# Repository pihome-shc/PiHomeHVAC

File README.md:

# MaxAir - Smart Thermostat

### Note: Now at Version 3.23

The previous version, PiHome, was centered around the creation of zones, this version is more centered around devices.

Version 1.1 introduces the 'Switch' zone category. These zones uses a binary switch sensor to control a zone relay and can be used to perform Home Automation tasks.

Version 1.2 Introduces the ability the control schedules based on local Sunset and Sunrise times. The existing 'Switch' zone category has been refined and the binary switch sensor is now classed the same as the Immersion and Humidity zone types.

The new 'Switch' zone category is used when no sensor or system controller are used, examples are:
* A lamp which switches on and off at set times
* A lamp which switches on a sunset and off at some set time
* A security light which switches on at sunset and off at sunrise on the following day

Version 1.3 Introduces support for MQTT Devices, together with Home Assistant Integration.

Version 1.4 Introduces support for multi-zone HVAC systems, together with 3 timer options - HEAT, COOL and AUTO (switch between HEAT and COOL as required).

Version 1.5 Introduced the use of Pump Relays to control the useage of external pumps.

Version 1.6 Introduces Email Notifications for Sensors when they return values either above of below pre-set limits.

Version 1.61 Introduces Away Scheduling, where a single overriding schedule can be activated by the Away Option.

Version 1.7 Introduces a revised Settings Menu option, to improve performance.

Version 1.71 Introduces an option to display a graph when either a Zone or Standalone Sensor tile is clicked. In the case of a Zone tile, buttons on the popup dialogue allow the selection of eithera 24hour or 1hour period graph display, in the case of a standalone sensor, a 24hour period graph will be displayed. The graph popup has buttons to allow swapping between 1hour and 24hour displays.

Version 1.80 Introduces a revised Home screen, which no longer auto-refreshes. The data and indicator fields on the screen are updated individually once every second. The result is that now any pop-up windows that are opened, will remain displayed until closed by the user. 

Version 2.01 Major update that introduces 'Colour Themes' and a new look based around the use of Bootstrap Version 5.2. Six different colour themes are available, Amber, Blue, Orange, Red, Teal and Violet.

Version 2.02 Introduces a simplified 'theme' definition, adds theme coloring to dropdown lists and adds Dark and Burnt Orange themes.

Version 2.03 Introduces 'Cooling' type zones that work witha temperture sensor, zone relay/s and operature againt a negative temperature profile.

Version 2.04 Introduces 'Message Sensors', to allow Home Screen display of custom messages (example boiler status passed from external interface).

Version 2.05 Introduces 'eBUS Communication', to allow MaxAir to capture data from eBUS compliant Boilers.

Version 2.06 Introduces the ability to attach the Live Temperature Control to any desired zone and the ability to configure any 'Immersion' or 'Cooling'zone (zone types with no System Controller attached) to maintain the set default temperature when there is no active schedule.

Version 2.07 Introduces 'Relay ON Lag Time', to allow relays to be triggered to the ON state after a preset delay is applied to the initial trigger ON request.

Version 3.00 Major Update - main processing engine 'controller.php' replace by Python3 module 'controller.py', runs continually every 1 second to improve system respose time

Version 3.01 Update Bootstrap from Version 5.2.3 to 5.3.2 and Bootstrap Icons from Version 1.10.3 to 1.11.0

Version 3.02 Change to the operation of cascading popup screens where they now return to the previous popup, rather than returning to the originating 'Settings' menu screen. This release also contains minor bug fixes.

Version 3.03 Introduces Graph Archiving. Optionally all sensors which generate a graph can be archived to a CSV file at midnight each day, the storage path can be set to any location prefered. Additionally a new Graph category, Min/Max, has been added, it used the data from the archive file to display separate graphs for the minimum and maximum sensor readings on a daily basis.

Version 3.04 Adds support for MySensor relay sketches which use 'Heartbeat' signals ie. the WT32-ETH01 adapter where the sketch version is > 0.37 and the Zone Controller or Multi Controller where the sketch version is > 0.33. For these adapters the relay state will only be updated on change rather than being continually rewrite, additionally any unallocated relays will be restored to the OFF state by the 'Heartbeat' process.

Version 3.05 Changes to ESP32-ETH01 Gateway Controller sketch to only write updates on state change. Rollup of various bug fixes.

Version 3.06 Remove dependancy on paho-mqtt Version 1.5. Changes to Multi-Controller sketch.

Version 3.07 Adds support zones with multiple sensors, using average sensor temperature reading. Update to Bootstrap Version 3.5.7.

Version 3.08 Change to Notification EMail to add timestamps.

Version 3.09 Bug Fix to ensure that if a system power failure occurs during a zone overrun phase, then the system will return with the zone relay switched OFF.
Update – if zone, or sensor, or relay edit is initiated from the Settings menu, then after committing the change, the user is returned to the popup menu from which the edit was initiated.

Version 3.10 Improvements in display and processing of multi-sensor zones, includes a new table 'sensor_average'.

Version 3.11 User account management revised, to create three distint levels of access to the system; Level 0 - system administrator, with full access to the system, Level 1 - user with configuration access to the system and Level 2 - user with display only access. Support added for the 'Olimex Gateway', which functions as a gateway plus relay controller plus multiple DS18B20 sensor support.

Version 3.12 Enable multiple relays controllers to be attached to a single sensor being used for 'Frost Control'. Add initial support for ZigBee sensors using MQTT and Zigbee2MQTT.

Version 3.13 Change to Min/Max graph process to use a table to hold daily minimum and maximum vales for all sensors set to procuce a graph (rather than a csv file).

Version 3.14 New Feature, 'One Shot Boost' boost will terminate once the target temperature is reached.

Version 3.15 Bug Fix. Increase field size of colume 'zone_mode' in table 'relay_logs'.

Version 3.16 New Features, Stand-alone relays (relays not attached to a zone can be displayed on the Home Screen and their 'state' toggled by clicking on the tile), new GUI Settings/Node and Zone Configuration/Zone Indexing (to edit Home Screen tile placement of Zone and Add-On Zone tiles) and new GUI Settings/Device Configuration/Device Indexing (to edit Home Screen tile placement of Stand-alone Sensor and Stand-alone Relay tiles).

Version 3.17 Update Bootstrap to version 5.3.8

Version 3.18 New Feature, a local language file can be created to hold variations to the default language file.

Version 3.19 New Feature, Smart Off - Zone state will not re‑activate within a set number of minutes of a schedule end time.

Version 3.20 New Feature, Relay Messages - Enable custom messages to be displayed in the lower right hand corner of Stand Alone Relay tiles.

Version 3.21 New Features and Bug Fixes, Relay Schedules - Enable the creation of schedules for Stand Alone relays which operate in the same way as Zone schedules, Relay Groups - Enable the grouping of relays so that conditions applied to any relay in the group are applied to all relays in the same group, MQTT Relay Support - enhancements to the handling of MQTT relays so that returned state messages can be used with Relay Messages to create an indication of the MQTT relay's actual state (rather than what state MaxAir has tried to set the relay to), Home Screen layout - removal of the copywrite and title text from the Home screen and creation of a top left 'MaxAir' logo, which can be used as a Home button, EMail Setup Password - bug fix so that an unencrypted password is loaded when the Email popup screen opens plus the ability to display the password in plain text, Page Footer Text - weather and schedule text shown in larger bold text.

Version 3.22 New Features, Hot Water Weather Compensation - Override the schedule temperature for the Hot Water zone with a value derived from an algorithm using a control temperature (eg. the Weather Channel outside temperature) and a set of coefficients. Disabled Active Schedule Icon - display an icon in the lower right hand corner of a zone tile to indicate that a schedule which should be active at that time has been disabled.

Version 3.23 New Features, 'Return to Home Page' – if the system is left displaying any Settings menu screen, the Schedule list screen or the One Touch screen for longer than a configurable timeout period, then the display will return to the Home Screen. The timeout can be configured from the 'Settings/system Maintenance/Page Refresh' menu option, selecting a value of '0' will disable the timeout. The default is 60 second timeout. 'Temperature Delta' – new menu option 'Settings/System Status/Temp Delta', to display the Max, Min and Delta values by either Zone or Sensor over the preceding one or twenty four hour time interval and 'Disable schedules during summer months' – disable selected schedules during a set period of time, popup to define the period and a 'OneTouch' button to enable/disable the feature.
Additional APIs - see documentaion.
Update – Improve database update synchronisation.

## Setup:

* Add Nodes (as per PiHome)
* Create Temperature Measurement devices (with a node and child id)
* Create Relay devices (with a node and child id)
* Create Zones using the temperature measurement and relay devices created previously
* Temperature Measurement devices can be displayed without the need to be allocated to a 'zombie' zone

* The Temperature Measurement and Relay devices can be created from the One Touch menu

* New configuration GUIs are available for the Relays and Sensors devices

* Part of the reason for this version is to support HVAC systems and hence the system can be configured to work in either the existing Boiler or HVAC mode. The mode is selected from settings/system configuration menu

* The home screen will show the mode of operation

* The 'MODE' button will cycle through the various modes of operation, for Boiler mode this is OFF, TIMER, CE, HW or BOTH, for HVAC the modes are OFF, TIMER, AUTO, HEAT, COOL or FAN.

### The trusted boiler.php engine has been replaced by controller.php

## Requirements
Basic knowledge of command line with following main components for MaxAir to function.
* Either the Debian or Ubuntu or ArchLinux Operating System
* Apache Web Server
* PHP 7.x or higher
* Python 3.x
* MySQL/MariaDB
* Adafruit Blinka

## Supported Single Board Computers
The core requirements for the SBC are as stated above, MaxAir has been successfully installed on the following SBCs :
* Raspberry Pi Zero and Raspberry Zero W 
* Raspberry Pi 3/3B
* Raspberry Pi 4
* Orange Pi Zero
* Orange Pi Zero LTS
* Orange Pi Zero Plus
* Orange Pi Zero Plus2 H5 (with eMMC on-board storage)
* Orange Pi Zero2
* Orange Pi 3 (with optional eMMC on-board storage)
* Orange Pi 3 LTS (with eMMC on-board storage)
* Orange Pi 4 (with optional eMMC on-board storage)
* Orange Pi 4 LTS (with eMMC on-board storage)
* Orange Pi 5
* Rock Pi E (with optional eMMC on-board storage)
* Pine H64 Model B (with optional eMMC on-board storage)
* Bannana Pi BPI-M2 Zero
* BeagleBone Black and BeagleBone Green (with eMMC on-board storage)

## How To Install
MaxAir can be installed on both Debian/Ubuntu or ArchLinux operating systems, the pre-requisite in both instances is a functioning LAMP stack (Linux, Apache, MySQL and PHP).

To install on Debian/Ubuntu:
* sudo rm -R /var/www
* sudo apt -y install git
* sudo git clone https://github.com/twa127/PiHomeHVAC.git "/var/www"
* sudo chown -R www-data:www-data /var/www
* cd /var/www/prerequisites
* sudo bash ./install.sh (accept all defaults, when asked to enter a new password for the mariadb us passw0rd)

To install on ArchLinux:
* sudo rm -R /srv/http
* sudo pacman -S git
* sudo git clone https://github.com/twa127/PiHomeHVAC.git "/srv/http"
* sudo chown -R http:http /srv/http
* cd /srv/http/prerequisites
* sudo bash ./install.sh (accept all defaults, when asked to enter a new password for the mariadb us passw0rd)
* Note: setup.php will create a symbolic link /var/www to /srv/http, for compatibility

## Secial Thanks to

* [Bootstrap](https://getbootstrap.com/ "Bootstrap ")
* [Pretty Checkbox](http://www.cssscript.com/pretty-checkbox-radio-inputs-bootstrap-awesome-bootstrap-checkbox-css "Pretty Checkbox ")
* [Box Shadow CSS](http://www.cssmatic.com/box-shadow "Box Shadow CSS")
* [AnimateCSS](https://daneden.github.io/animate.css "Animate.css ")
* [MySensors](https://www.mysensors.org "MySensors")
* [RaspberryPi Home Automation](http://pihome.harkemedia.de "RaspberryPi Home Automation")
* [All Others if forget them...](http://www.pihome.eu "All Others if forget them...")

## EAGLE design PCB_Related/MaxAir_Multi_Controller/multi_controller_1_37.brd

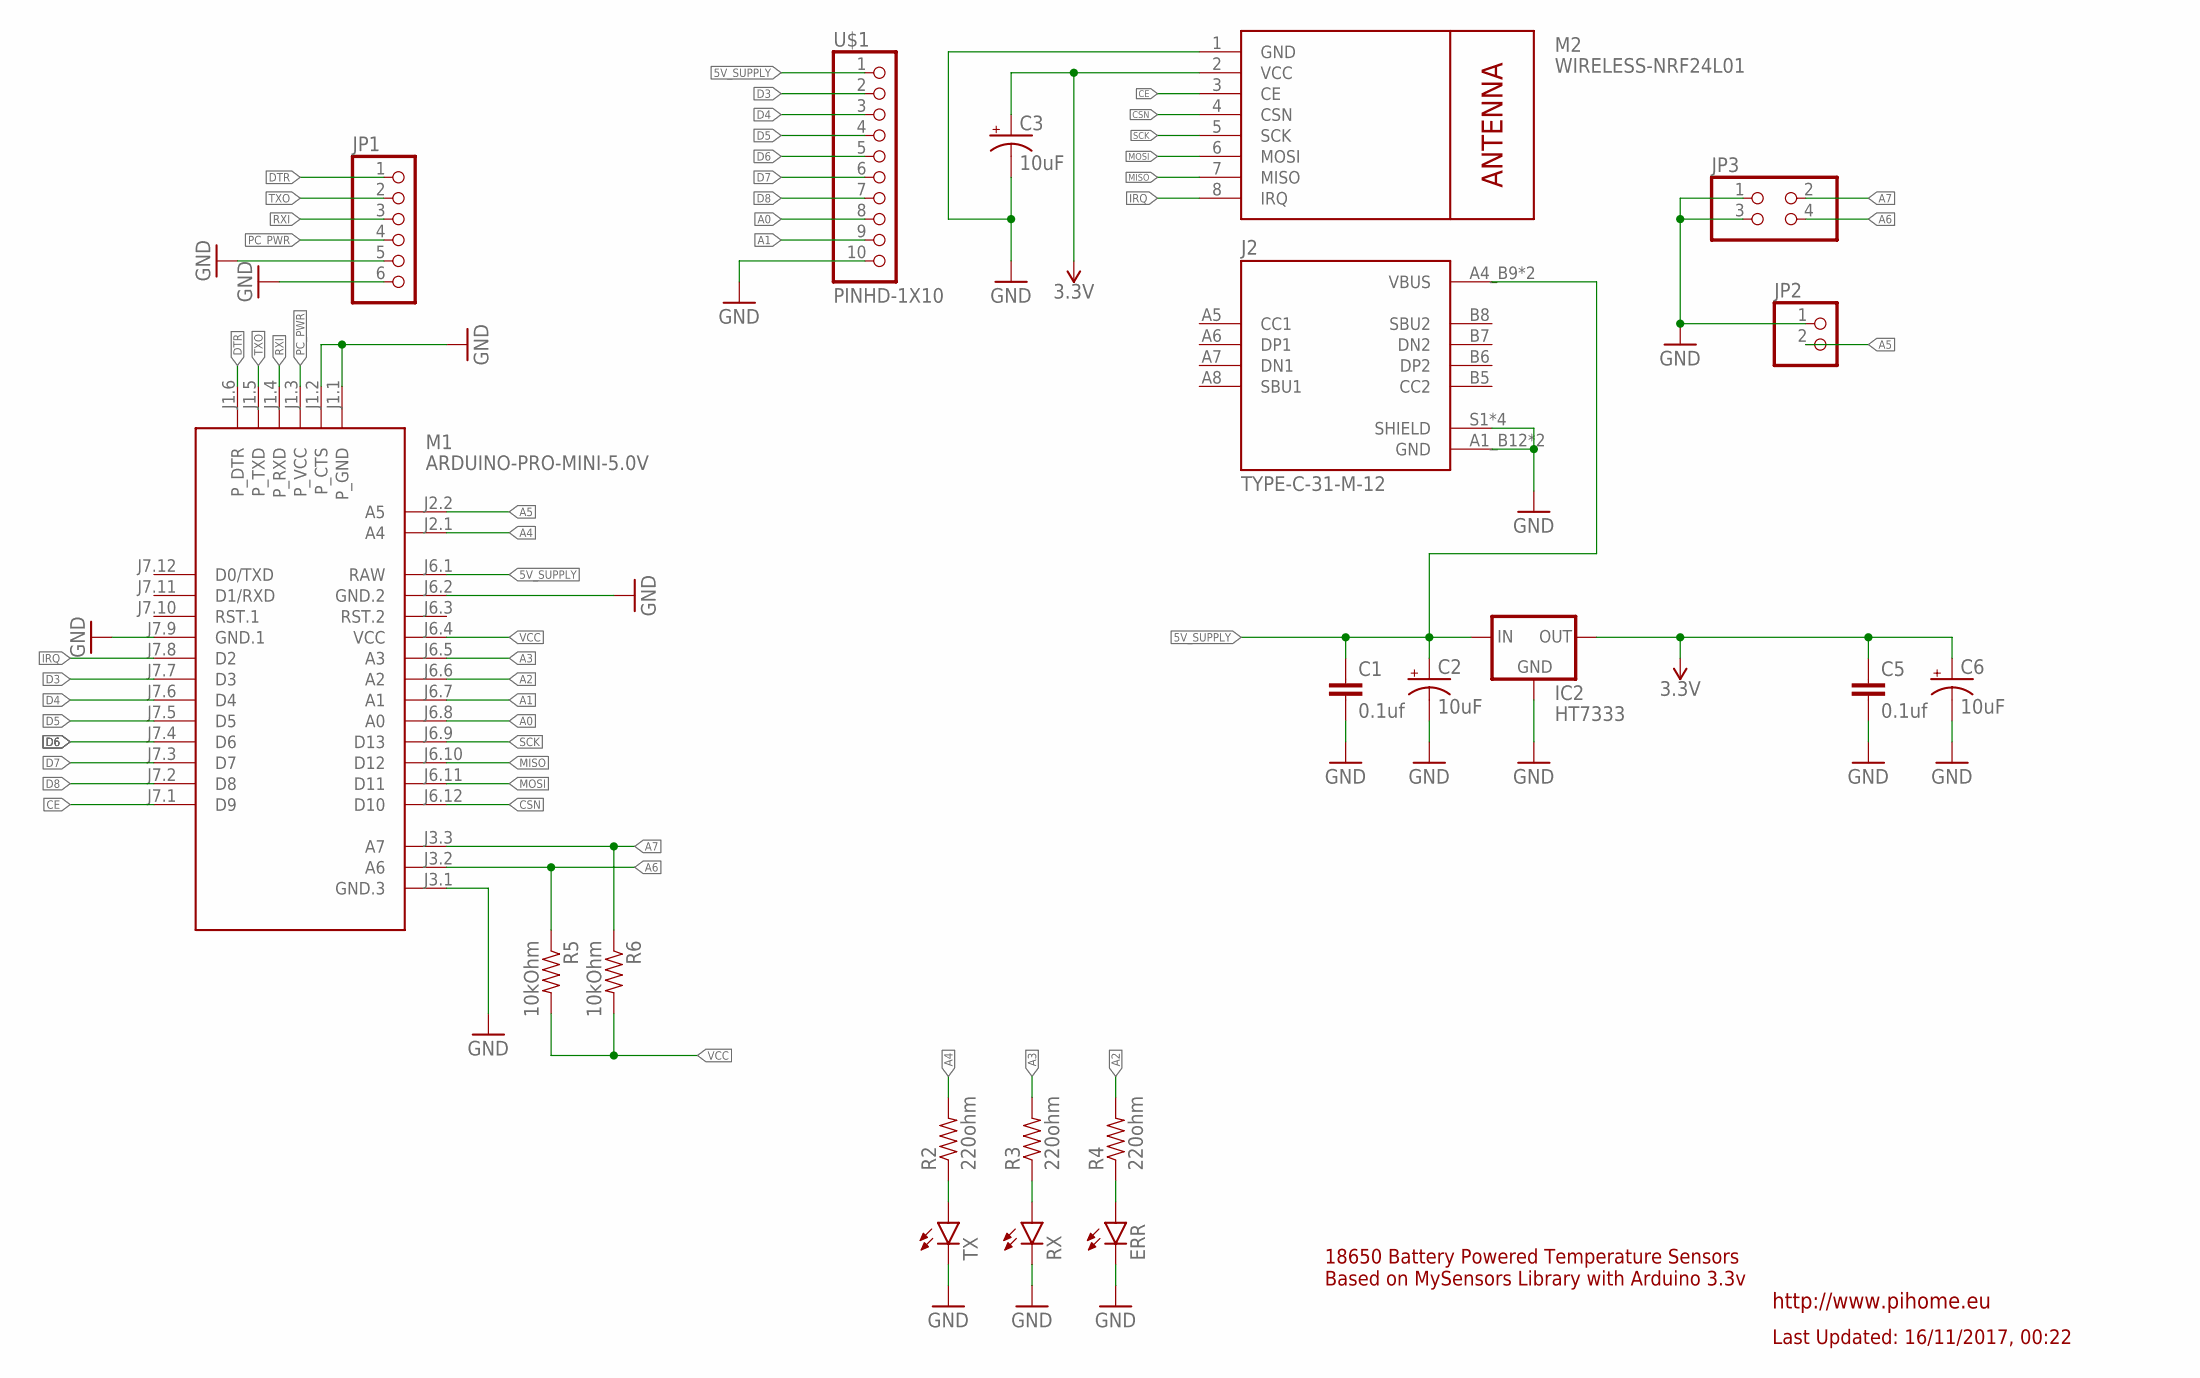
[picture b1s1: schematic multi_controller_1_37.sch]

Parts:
C1, C5: 0.1uf; CAP-PTH-SMALL-KIT
C2, C3, C6: 10uF; CPOL-RADIAL-10UF-25V-KIT
ERR: LED3MM
IC2: HT7333; SOT-89
J2: TYPE-C-31-M-12; HRO_TYPE-C-31-M-12
JP1: PINHD-1X6; 1X06
JP2: PINHD-1X2; 1X02
JP3: PINHD-2X2; 2X02
M1: ARDUINO-PRO-MINI-5.0V; ARDUINO-PRO-MINI
M2: WIRELESS-NRF24L01
R2, R3, R4: 220ohm; AXIAL-0.3
R5, R6: 10kOhm; AXIAL-0.3
RX: LED3MM
TX: LED3MM
U$1: PINHD-1X10; 1X10-BIG

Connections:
3.3V: C3.1 (+), C5.1, C6.1 (+), IC2.1 (OUT), M2.2 (VCC)
5V_SUPPLY: C1.1, C2.1 (+), IC2.3 (IN), IC2.4 (IN), J2.A4_B9 (VBUS), J2.B4_A9 (VBUS), M1.J6.1 (RAW), U$1.1
A0: M1.J6.8 (A0), U$1.8
A1: M1.J6.7 (A1), U$1.9
A2: M1.J6.6 (A2), R4.P$2 (2)
A3: M1.J6.5 (A3), R3.P$2 (2)
A4: M1.J2.1 (A4), R2.P$2 (2)
A5: JP2.2, M1.J2.2 (A5)
A6: JP3.4, M1.J3.2 (A6), R5.P$1 (1)
A7: JP3.2, M1.J3.3 (A7), R6.P$1 (1)
CE: M1.J7.1 (D9), M2.3 (CE)
CSN: M1.J6.12 (D10), M2.4 (CSN)
D3: M1.J7.7 (D3), U$1.2
D4: M1.J7.6 (D4), U$1.3
D5: M1.J7.5 (D5), U$1.4
D6: M1.J7.4 (D6), U$1.5
D7: M1.J7.3 (D7), U$1.6
D8: M1.J7.2 (D8), U$1.7
DTR: JP1.1, M1.J1.6 (P_DTR)
GND: C1.2, C2.2 (-), C3.2 (-), C5.2, C6.2 (-), ERR.K (C), IC2.2 (GND), J2.A1_B12 (GND), J2.B1_A12 (GND), J2.S1 (SHIELD), J2.S2 (SHIELD), J2.S3 (SHIELD), J2.S4 (SHIELD), JP1.5, JP1.6, JP2.1, JP3.1, JP3.3, M1.J1.1 (P_GND), M1.J1.2 (P_CTS), M1.J6.2 (GND.2), M1.J7.9 (GND.1), M2.1 (GND), RX.K (C), TX.K (C), U$1.10
IRQ: M1.J7.8 (D2), M2.8 (IRQ)
MISO: M1.J6.10 (D12), M2.7 (MISO)
MOSI: M1.J6.11 (D11), M2.6 (MOSI)
unnamed: R2.P$1 (1), TX.A
unnamed: R3.P$1 (1), RX.A
unnamed: ERR.A, R4.P$1 (1)
PC_PWR: JP1.4, M1.J1.3 (P_VCC)
RXI: JP1.3, M1.J1.4 (P_RXD)
SCK: M1.J6.9 (D13), M2.5 (SCK)
TXO: JP1.2, M1.J1.5 (P_TXD)
VCC: M1.J6.4 (VCC), R5.P$2 (2), R6.P$2 (2)

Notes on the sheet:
18650 Battery Powered Temperature Sensors Based on MySensors Library with Arduino 3.3v
Last Updated: 16/11/2017, 00:22
http://www.pihome.eu

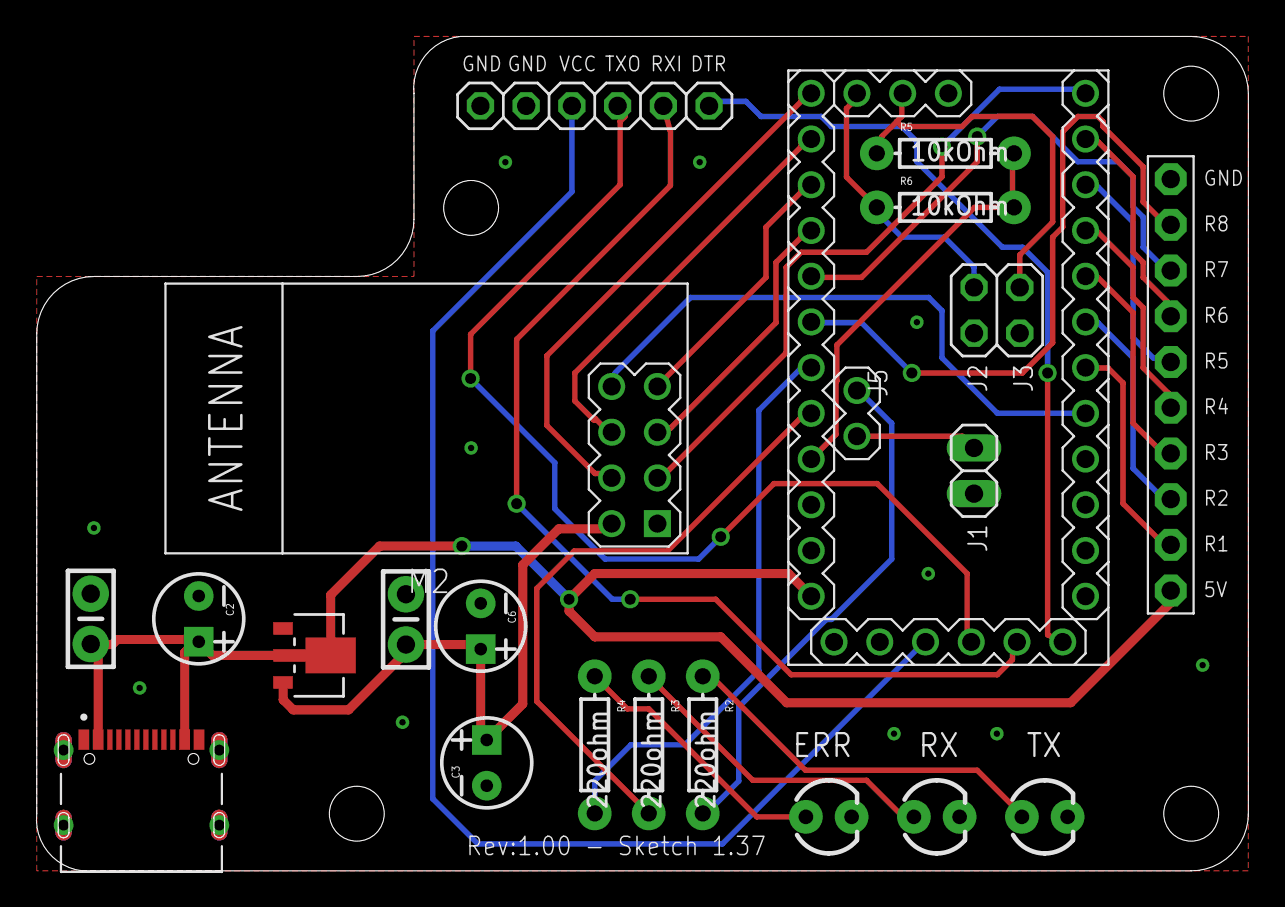
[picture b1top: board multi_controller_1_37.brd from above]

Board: 2 copper layers, 67.3 x 46.4 mm, 22 parts (1 on the bottom side), 31 nets.

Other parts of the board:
LOGO1: OSHW-LOGOL; OSHW-LOGO-L

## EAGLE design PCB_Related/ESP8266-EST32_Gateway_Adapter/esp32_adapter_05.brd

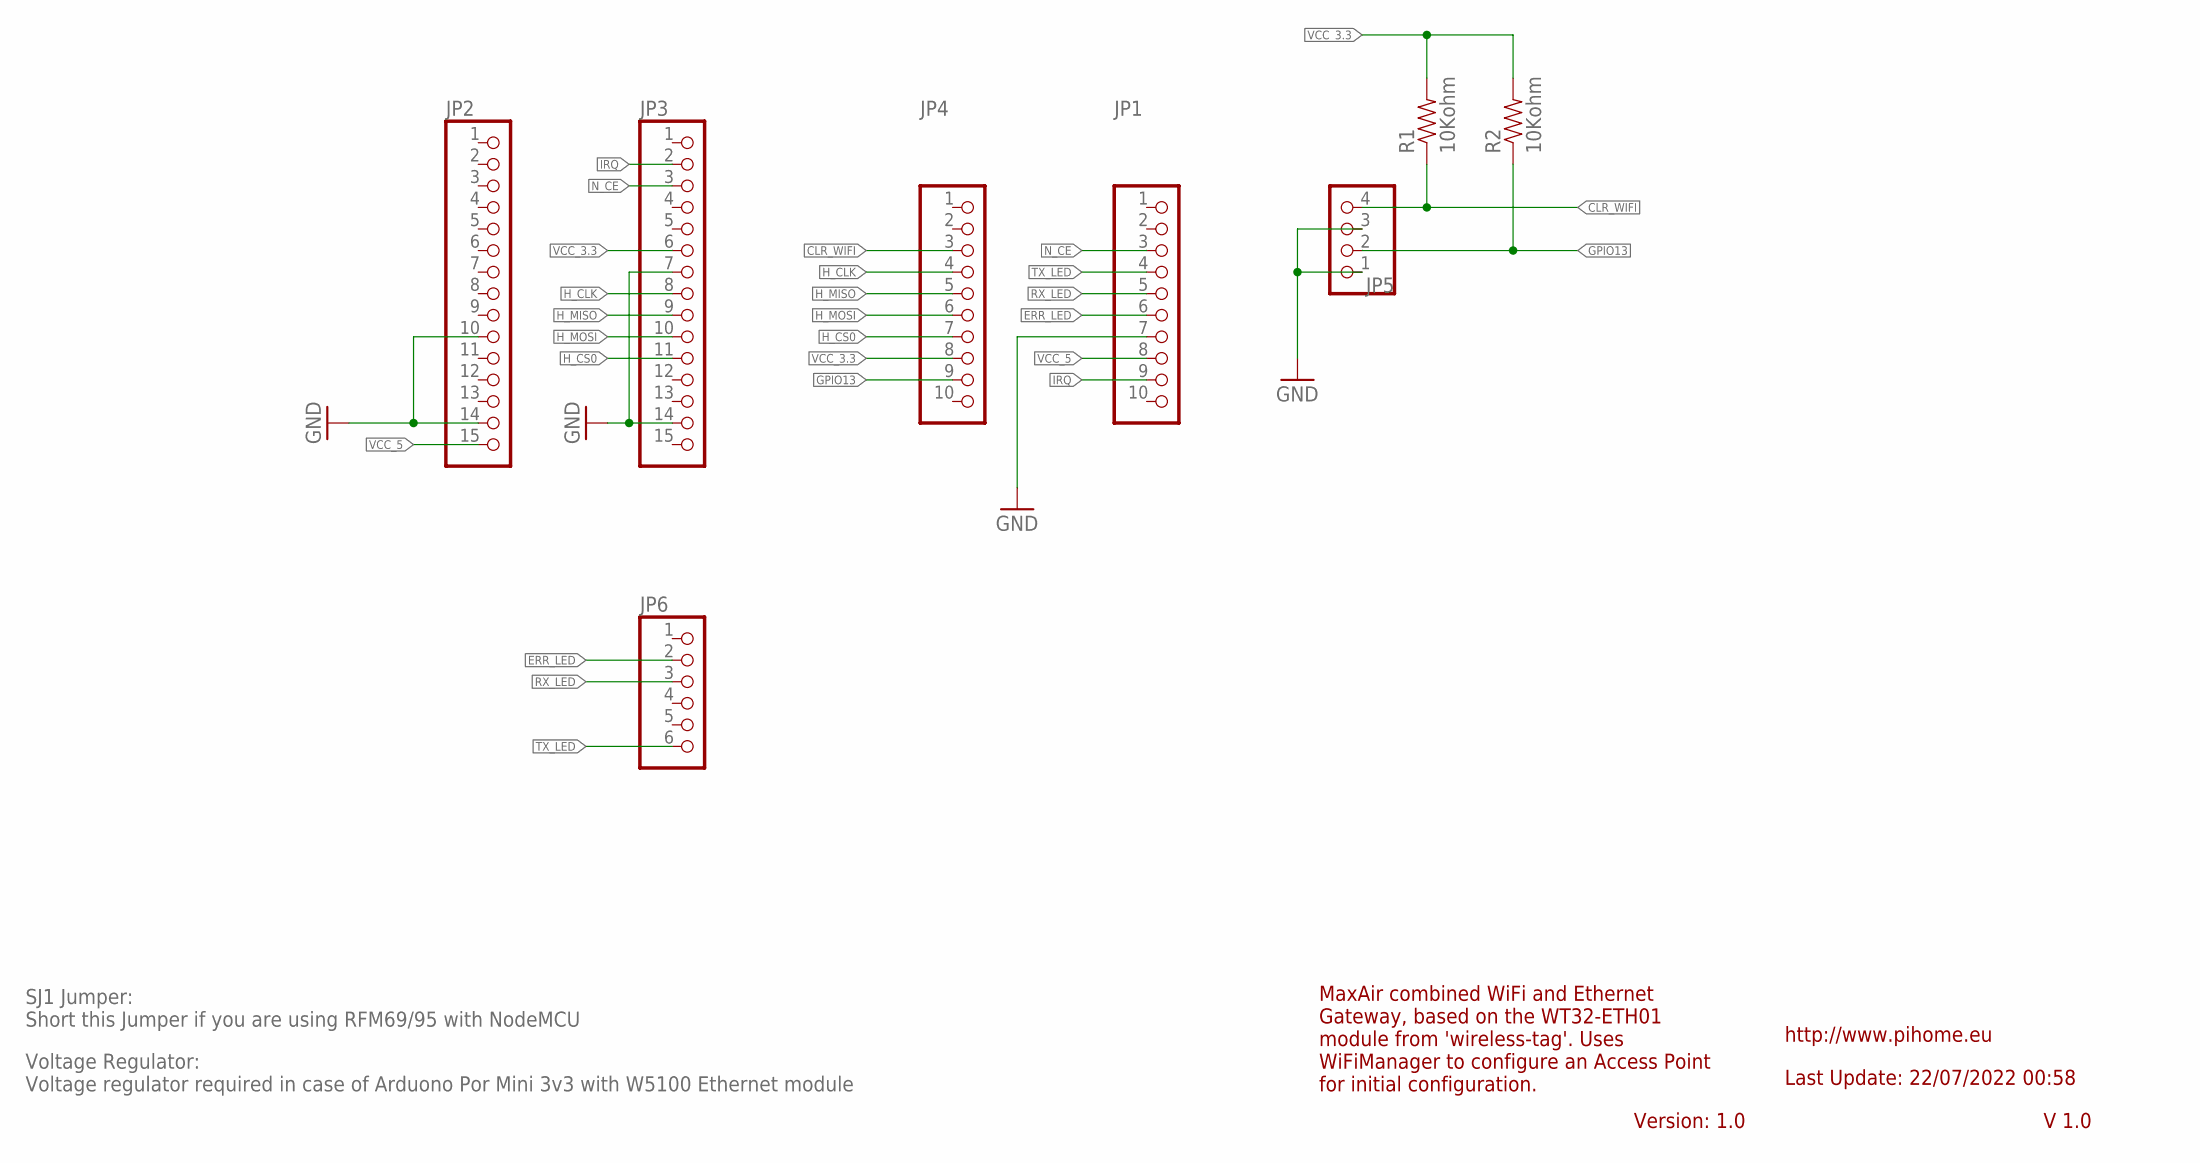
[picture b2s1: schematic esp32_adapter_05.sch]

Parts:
JP1, JP4: PINHD-1X10; 1X10-BIG
JP2, JP3: PINHD-1X15-CB; 1X15-CB
JP5: PINHD-1X4/90; 1X04/90
JP6: PINHD-1X6CLEAN; 1X06-CLEAN
R1, R2: 10Kohm; AXIAL-0.3

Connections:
CLR_WIFI: JP4.3, JP5.4, R1.P$1 (1)
ERR_LED: JP1.6, JP6.2
GND: JP1.7, JP2.10, JP2.14, JP3.7, JP3.14, JP5.1, JP5.3
GPIO13: JP4.9, JP5.2, R2.P$1 (1)
H_CLK: JP3.8, JP4.4
H_CS0: JP3.11, JP4.7
H_MISO: JP3.9, JP4.5
H_MOSI: JP3.10, JP4.6
IRQ: JP1.9, JP3.2
N_CE: JP1.3, JP3.3
RX_LED: JP1.5, JP6.3
TX_LED: JP1.4, JP6.6
VCC_3.3: JP3.6, JP4.8, R1.P$2 (2), R2.P$2 (2)
VCC_5: JP1.8, JP2.15

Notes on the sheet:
http://www.pihome.eu
Last Update: 22/07/2022 00:58
MaxAir combined WiFi and Ethernet Gateway, based on the WT32-ETH01 module from 'wireless-tag'. Uses WiFiManager to configure an Access Point for initial configuration.
Version: 1.0
V 1.0
SJ1 Jumper: Short this Jumper if you are using RFM69/95 with NodeMCU
Voltage Regulator: Voltage regulator required in case of Arduono Por Mini 3v3 with W5100 Ethernet module

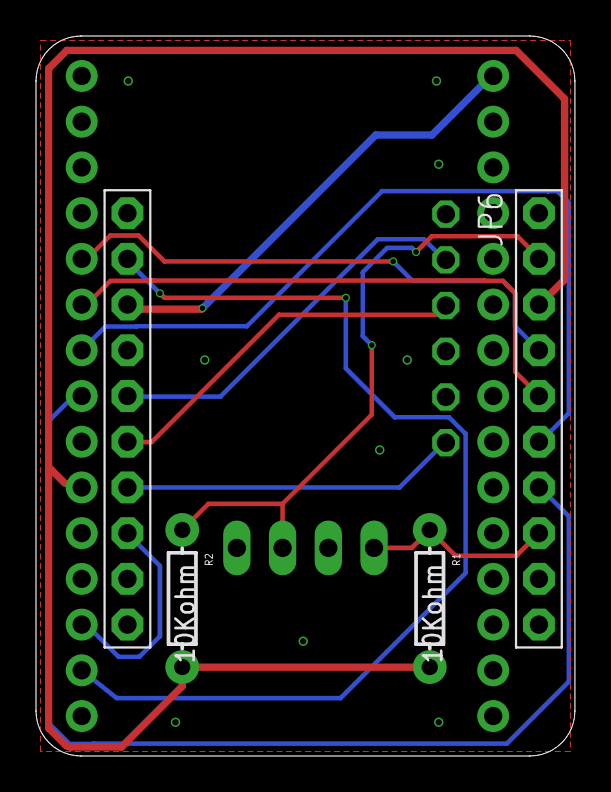
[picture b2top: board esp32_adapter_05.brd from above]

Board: 2 copper layers, 29.9 x 40.0 mm, 8 parts (1 on the bottom side), 14 nets.

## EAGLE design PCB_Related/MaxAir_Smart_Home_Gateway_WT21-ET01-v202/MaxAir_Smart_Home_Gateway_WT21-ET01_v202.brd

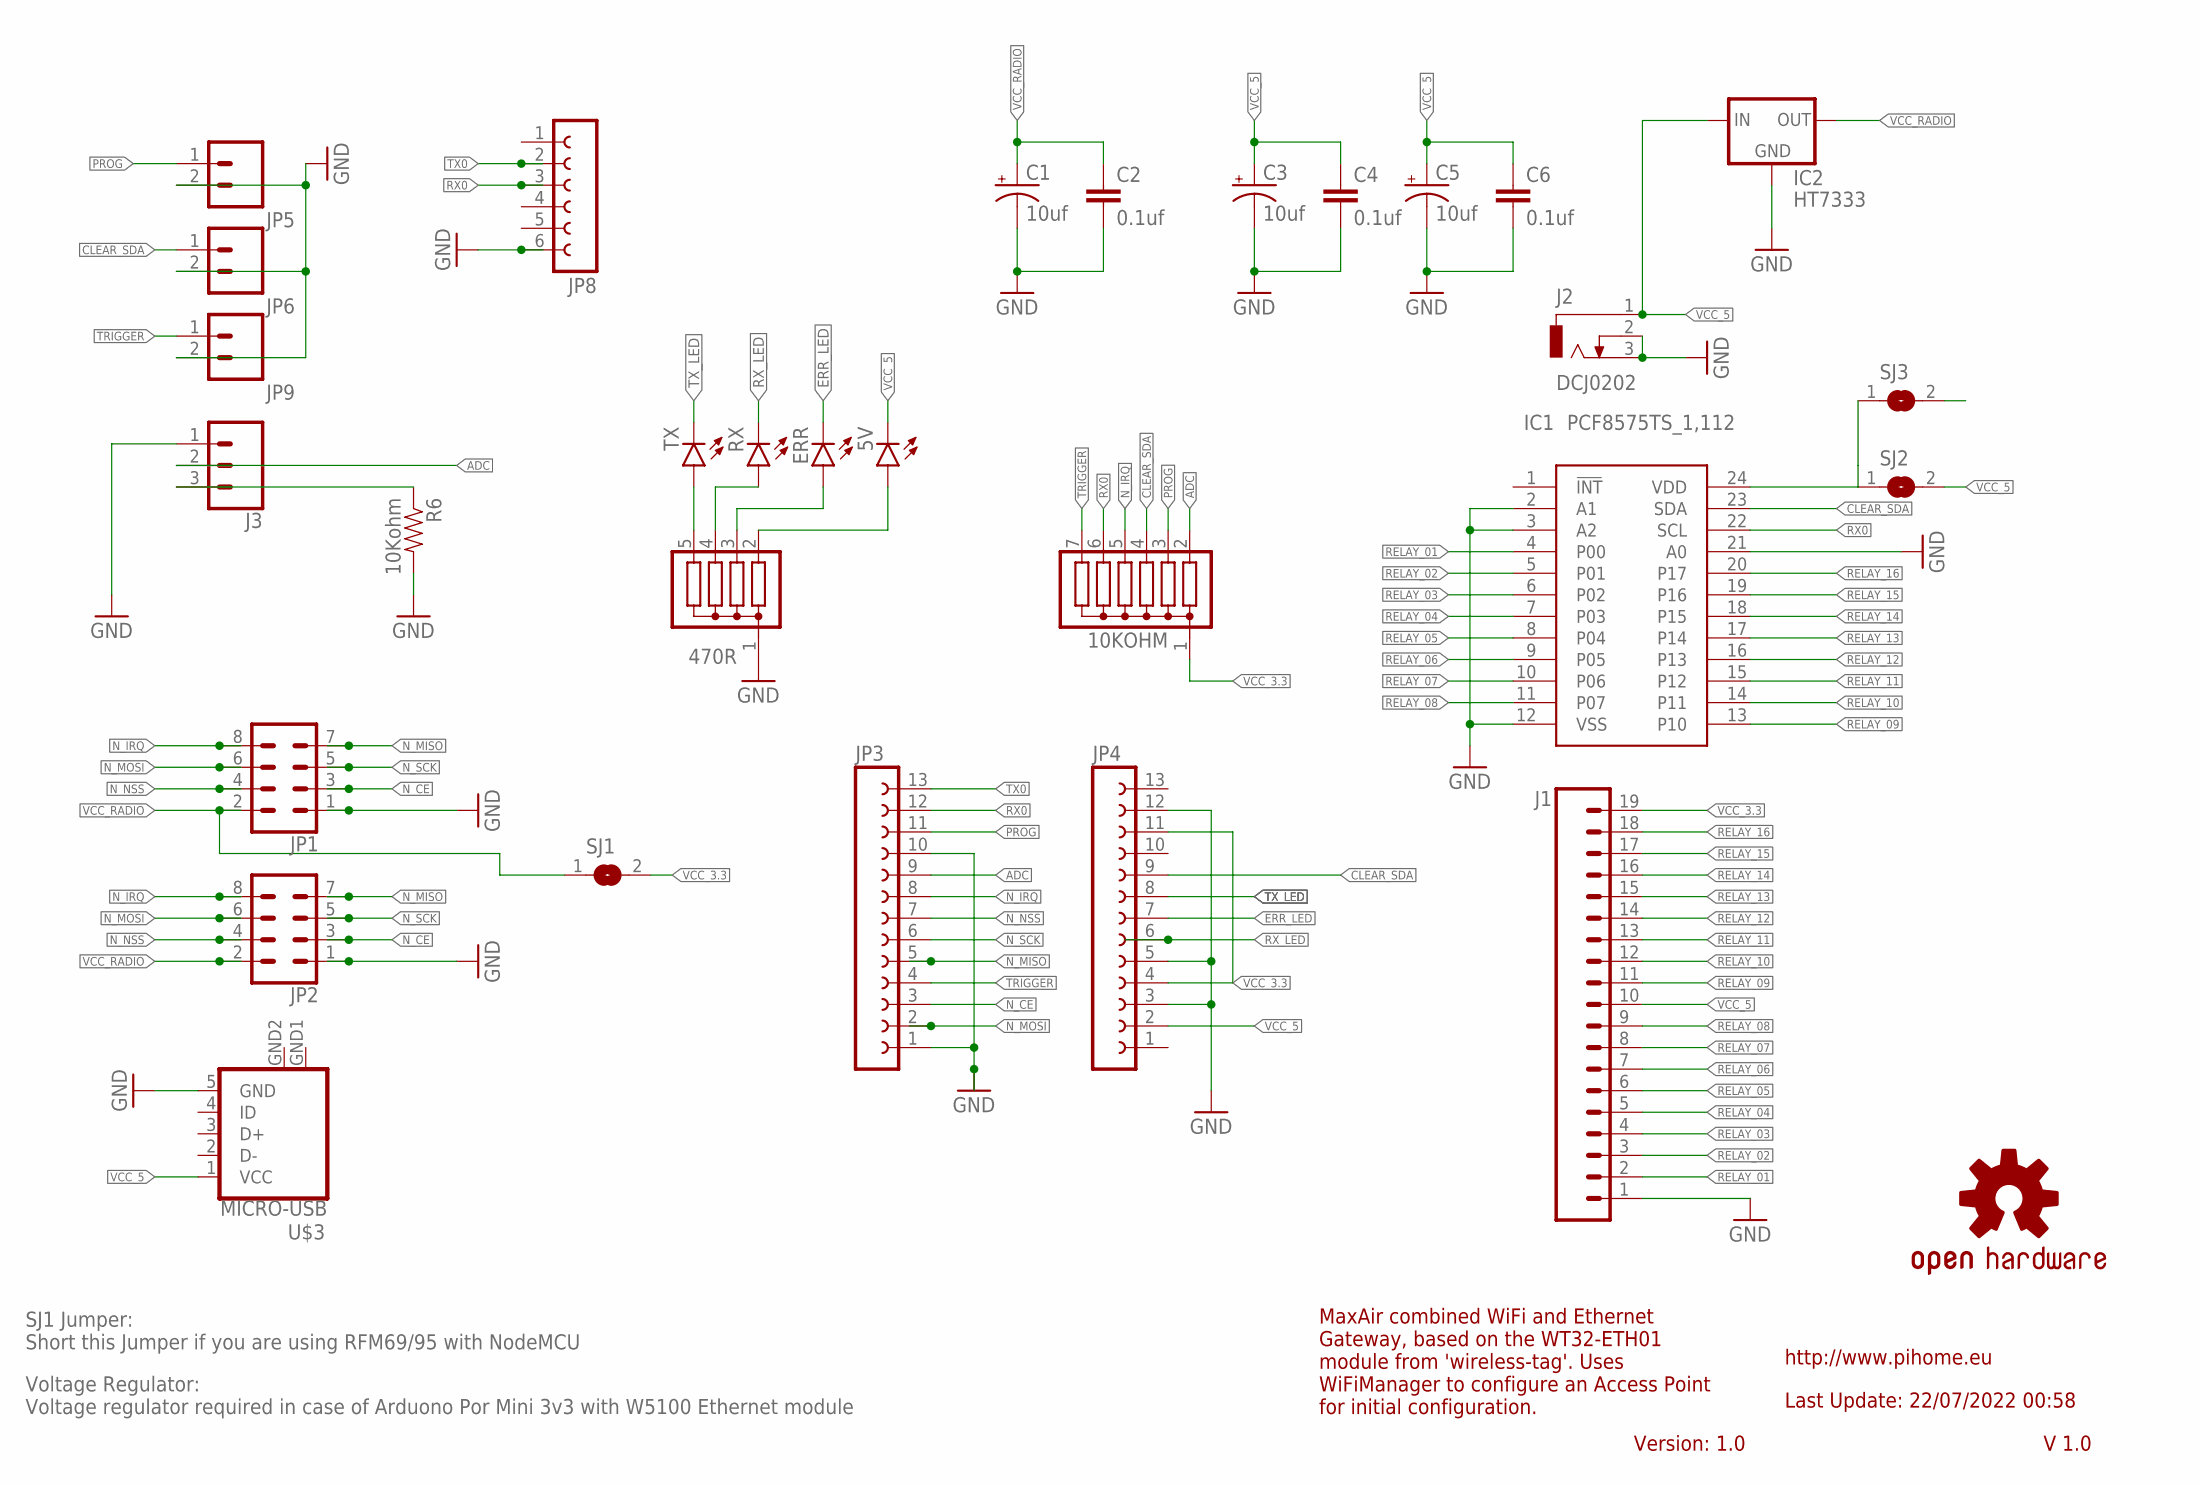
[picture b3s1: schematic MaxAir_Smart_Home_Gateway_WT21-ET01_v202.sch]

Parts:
5V: LED3MM
10KOHM: G06R; SIL7
470R: G04R; SIL5
C1, C3, C5: 10uf; CPOL-RADIAL-10UF-25V-KIT
C2, C4, C6: 0.1uf; CAP-PTH-SMALL-KIT
ERR: LED3MM
IC1: PCF8575TS_1,112; SOP65P775X200-24N
IC2: HT7333; SOT-89
J1: CONN_19; 1X19
J2: DCJ0202
J3: CONN_03; 1X03
JP1, JP2: CONN_04X2; 2X4
JP3, JP4: FE13-1; FE13
JP5, JP6, JP9: CONN_02; 1X02
JP8: FE06-1; FE06
LOGO1: OSHW-LOGOMINI; OSHW-LOGO-MINI
R6: 10Kohm; AXIAL-0.3
RX: LED3MM
SJ1, SJ2, SJ3: SJ
TX: LED3MM
U$3: MICRO-USB

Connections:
8575: IC1.24 (VDD), SJ2.1, SJ3.1
ADC: 10KOHM.2, J3.2, JP3.9
CLEAR_SDA: 10KOHM.4, IC1.23 (SDA), JP4.9, JP6.1
DIS_ETH: J3.3, R6.P$1 (1)
ERR_LED: ERR.K (C), JP4.7
GND: 470R.1, C1.2 (-), C2.2, C3.2 (-), C4.2, C5.2 (-), C6.2, IC1.2 (A1), IC1.3 (A2), IC1.12 (VSS), IC1.21 (A0), IC2.2 (GND), J1.1, J2.2, J2.3, J3.1, JP1.1, JP2.1, JP3.1, JP3.10, JP4.3, JP4.5, JP4.12, JP5.2, JP6.2, JP8.6, JP9.2, R6.P$2 (2), U$3.5 (GND), U$3.GND1 (GND), U$3.GND2 (GND)
unnamed: 470R.5, TX.A
unnamed: 470R.4, RX.A
unnamed: 470R.3, ERR.A
unnamed: 5V.A, 470R.2
N_CE: JP1.3, JP2.3, JP3.3
N_IRQ: 10KOHM.5, JP1.8, JP2.8, JP3.8
N_MISO: JP1.7, JP2.7, JP3.5
N_MOSI: JP1.6, JP2.6, JP3.2
N_NSS: JP1.4, JP2.4, JP3.7
N_SCK: JP1.5, JP2.5, JP3.6
PROG: 10KOHM.3, JP3.11, JP5.1
RELAY_01: IC1.4 (P00), J1.2
RELAY_02: IC1.5 (P01), J1.3
RELAY_03: IC1.6 (P02), J1.4
RELAY_04: IC1.7 (P03), J1.5
RELAY_05: IC1.8 (P04), J1.6
RELAY_06: IC1.9 (P05), J1.7
RELAY_07: IC1.10 (P06), J1.8
RELAY_08: IC1.11 (P07), J1.9
RELAY_09: IC1.13 (P10), J1.11
RELAY_10: IC1.14 (P11), J1.12
RELAY_11: IC1.15 (P12), J1.13
RELAY_12: IC1.16 (P13), J1.14
RELAY_13: IC1.17 (P14), J1.15
RELAY_14: IC1.18 (P15), J1.16
RELAY_15: IC1.19 (P16), J1.17
RELAY_16: IC1.20 (P17), J1.18
RX0: 10KOHM.6, IC1.22 (SCL), JP3.12, JP8.3
RX_LED: JP4.6, RX.K (C)
TRIGGER: 10KOHM.7, JP3.4, JP9.1
TX0: JP3.13, JP8.2
TX_LED: JP4.8, TX.K (C)
VCC_3.3: 10KOHM.1, J1.19, JP4.4, JP4.11, SJ1.2, SJ3.2
VCC_5: 5V.K (C), C3.1 (+), C4.1, C5.1 (+), C6.1, IC2.3 (IN), IC2.4 (IN), J1.10, J2.1, JP4.2, SJ2.2, U$3.1 (VCC)
VCC_RADIO: C1.1 (+), C2.1, IC2.1 (OUT), JP1.2, JP2.2, SJ1.1

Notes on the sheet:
http://www.pihome.eu
Last Update: 22/07/2022 00:58
MaxAir combined WiFi and Ethernet Gateway, based on the WT32-ETH01 module from 'wireless-tag'. Uses WiFiManager to configure an Access Point for initial configuration.
Version: 1.0
V 1.0
SJ1 Jumper: Short this Jumper if you are using RFM69/95 with NodeMCU
Voltage Regulator: Voltage regulator required in case of Arduono Por Mini 3v3 with W5100 Ethernet module

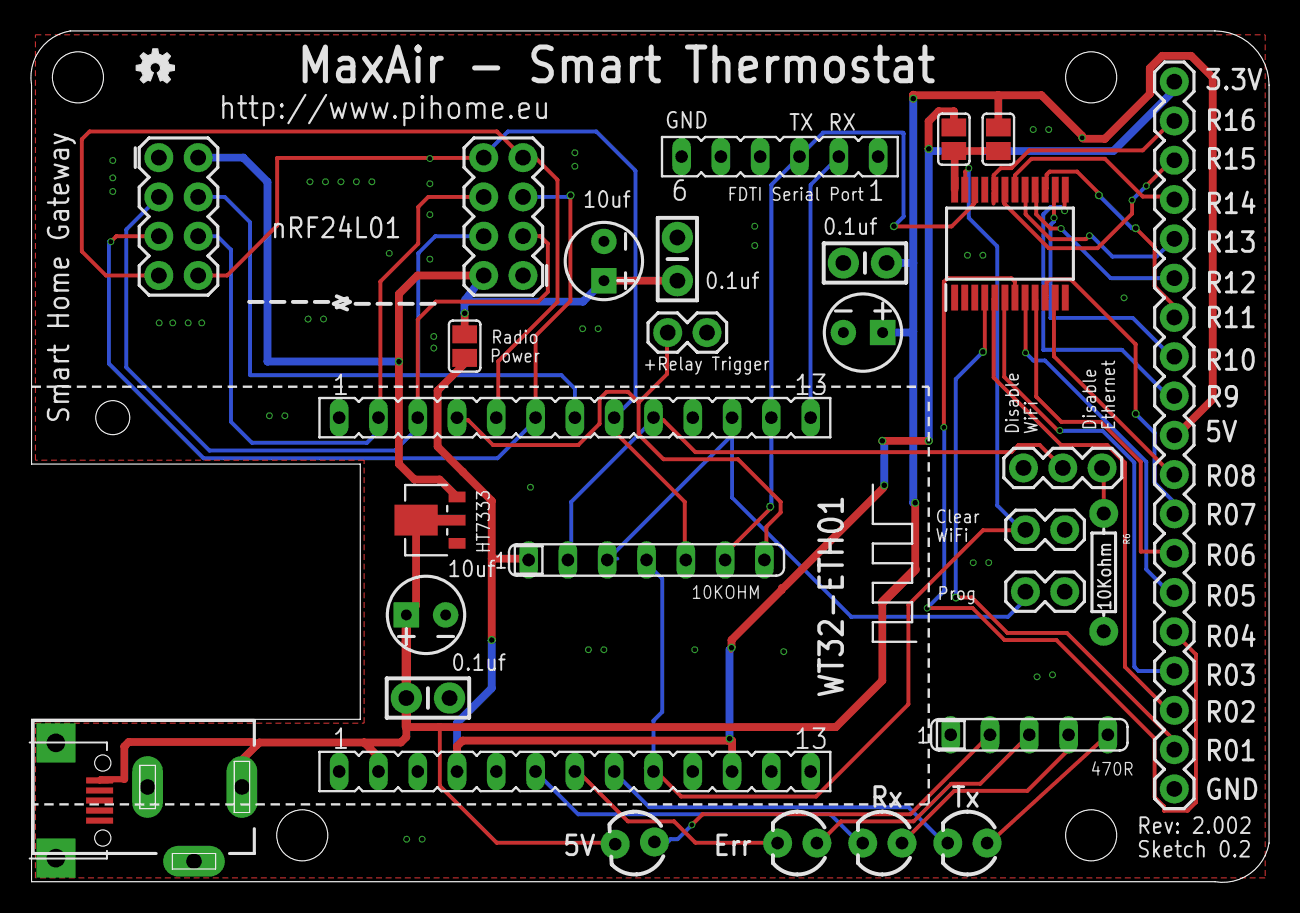
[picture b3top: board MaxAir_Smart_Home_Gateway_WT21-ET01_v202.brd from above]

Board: 2 copper layers, 80.0 x 55.0 mm, 35 parts (0 on the bottom side), 41 nets.

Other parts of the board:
U$1, U$2, U$4, U$5: STAND-OFF

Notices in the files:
Arduino_Sketches/nRF24L01/MaxAir_GatewayWT32_ETH01_v001/MaxAir_GatewayWT32_ETH01_v002.ino:
Copyright (C) 2013-2018 Sensnology AB
modify it under the terms of the GNU General Public License
parts and their libraries:
SparkFun-Capacitors: Licensing: Creative Commons ShareAlike 4.0 International - https://creativecommons.org/licenses/by-sa/4.0
diy-modules: Released under the Creative Commons Attribution 4.0 International License: http://creativecommons.org/licenses/by/4.0
